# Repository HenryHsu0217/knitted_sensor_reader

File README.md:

# Knitted Sensor Reader

## Introduction
This project contains the code and hardware setup for collecting data from knitted sensors. It includes simple examples of collected data with a 3x10 size sensor and a trained neural network for predicting the angle of the tested sensor. Additionally, code is provided for live evaluation for one or four sensors at a time with the trained neural network model.

## Table of Contents
- [Introduction](#introduction)
- [Features](#features)
- [Installation](#installation)
- [Setup](#setup)
    - [Hard ware setup](#hard-ware-setup)
        - [Robot arm setup and control](#robot-arm-setup-and-control)
        - [Xiao Seeed setup](#xiao-seeed-setup)
    - [WiFi setup](#wifi-setup)
- [Usage](#usage)
  - [Data Collection](#data-collection)
    - [Data Collection for one sensor](#data-collection-for-one-sensor)
    - [Data Collection for four sensor](#data-collection-for-four-sensor)
  - [Model Training](#model-training)
  - [Live Evaluation](#live-evaluation)
- [Examples](#examples)
## Features
- Collect data from knitted sensors
- Simple examples with 3x10 size sensor data
- Trained neural network model for angle prediction
- Live evaluation for one or four sensors simultaneously
## Installation
1. Clone the repository to your local machine:
   ```sh
   git clone https://github.com/HenryHsu0217/knitted_sensor_reader.git
    ```
2. Navigate to the project directory
3. Install the required dependencies:
    ```sh
    pip install -r requirements.txt
    ```
## Setup
### Hard ware setup
To set up the hardware for this project, you will need:  
- Knitted sensors
- Xiao Seeed ESP32C with custom PCB
- Connection wires
- Batteries
- Arduino Tinkerkit robot arm with sleeve and Ardino Uno
#### Robot arm setup and control
To setup and control the robot arm, please first go to https://docs.arduino.cc/retired/getting-started-guides/Braccio/ to check the essential library for the robot, after downloading the library, upload `Robot_arm.cpp` to the braod controling the arm. After uploading, you can control the robot arm to certain angle with serial input. Before entering the angle, please keep in mind that we are only controlling the ELBOW of the robot, and due to the setting of the arm, the arm will be at 0 degree with a setting of 45, so when entering the desired angle remember to add 45 to it. For example if you want the ELBOW to got to 60 degree, please enter 105 instead.
  
Attach the knitted sensor to the robot arm with pib needle to finish the robot arm setup.
### WiFi setup
The device that you are running the code with will be the server for the system, and make sure you are connected to private network, pubic network may cuase problem in connection.  

After your device is connected to a private netwrok and get your device's IP address update the SSID, password, and host ID accroding to your device in the `WiFi_Client.cpp` file for the Xiao Seeed broad. And also remember to update the host IP in `server_for_one.py`, `server_for_four.py`, `Live_Evalution_for_one.py`, and `live_Evalution_for_four.py` before running them with your device's IP.
#### Xiao Seeed setup
Upload `WiFi_Client.cpp` to the broad with the WiFi set correctly, insert the wires from the knitted sensor into the terminal and screw it tight. Plug in the battery and after the server is running press reset button on the broad to connect to the server.
  
After all the setups, you are ready to run the server for data collection, you can check the finished setup image of the robot arm in the `images` directory. Furthermore you can find files for the PCB in the `PCB` directory, you can open it with KiCad.
## Usage
### Data collection 
#### Data collection for one sensor
Before running the file `server_for_one.py` once again make sure the WiFi has been setup properly so that the port and host IP in `server_for_one.py` are the same in `WiFi_Client.cpp`. After uploading `WiFi_Client.cpp` to the braod and `server_for_one.py`.  

Run the server with:
```sh
python server_for_one.py
```  
After running the command line would show:
```sh
Server listening on 172.20.10.3:8080
starting user thread
Please input the file location for the data: 
```  
Enter the file location that you want to save the data(Ex: `datas/test_file`). After entering the file location the command line will ask to enter the current angle:
```sh
Please input angle: 
```
 After entering the angle, connect power to the Xiao Seed broad, if nothing happens press the reset button on the broad to make it retry on connecting to the WiFi. After it is connected to WiFi and connected to the server, the command line would show:
```sh
Server listening on 172.20.10.3:8080
starting user thread
Please input the file location for the data: test_file
Accepted connection from ('172.20.10.5', 51490)
```  
Than you can start collecting by entering `start` in the command line and press enter. Then the data will start logging and show the datas in the command line as:
```sh
Logging: 651 4088
Logging: 652 4090
Logging: 653 4092
Logging: 654 4091
Logging: 655 4092
```  
When finished, to save the file, simpliy enter `log` and press enter to save the file(the command line will keep refreshing the output so don't worry if your input is over write by the out put). Then you can find the data in the location that you defined earlier.  
  
After entering `log`, the process will stop, saving the file and start asking you for file location agian, you can continue with the next data collection directly with the same step: enter the desired location, enter start(no need for rest of the broad), enter `log` if finished. And if done with the entire process, enter `e` to stop the program and shut down the server.
#### Data collection for four sensor
For collecting data for four sensor, the process is simillar with the previous one, be fore running the `sever_for_four.py` file make sure the IP, port and other requirements are enter correclty for `sever_for_four.py` and `WiFi_Client.cpp`.  
  
Prepare 4 Xiao Seeed broad with code uploded to them, connect power to them and start the server with:
```sh
python sever_for_four.py
```  
After running the command line will show the same thing as:
```sh
Server listening on 172.20.10.3:8080
starting user thread
Please input the file location for the data: 
```  
Then same enter the file name and location you want to save the data. Then the command line will ask to enter the angles for the 4 sensors:
```sh
Please input angles separate with space: 
```
Enter the angle(Ex:10 20 30 40), the angles are the real angle of each broads, and how the broads are labeled is accroding to the sequence of the broad is connected to the server. For example is board 1 is connected first then it will be asigned with the angle label of 10 and so on.

Next press the reset button on the broads, and as they reset and connected to the server, the command line will output:
```sh
Waiting for connection: [1/4]
Waiting for connection: [2/4]
Waiting for connection: [3/4]
Waiting for connection: [4/4]
```
When all broad is connected, enter `start` and enter to start the data collection, then the command line will output the readings of the 4 broad:
```sh
Device  1 : 4092 Device  2 : 4089 Device  3 : 4094 Device  4 : 4091
```  
To save the data first enter `log`, this will stop the process and fetch the datas from all 4 broads, then enter `save` to save the file to the location entered earlier. And same after saving, the command line will ask you to enter the location for saving the data again, you can then start your next collection direclty by repeating the same process(there some time will have output bugs, which the output of the command line doesn't match what is mentioned above, but you can ignore it and follow the same input process).
### Model Training for one sensor
After data collection, a model can be trained with the data to predict the angle of the knitted senor. In the `NeuralNetwork` directory there is a pre-defined netwrork `Network_for_one.py` for training a model to predict the angle for only one sensor.  

Before training, since the data for one sensor is stored separated with different angle, we will want to mege them. To merge the data into single one for training, use the `merge.py` file in `datas/` which replace the file name in the code with the file directoryof your data, and it will merge the data into one and store into `datas/Merged`.  
  
After merging the data, you can replace the file name in `Train_for_one.py` to your merged data for training, and you can tune the hyperparameter there. After training, the trained model will be saved in `./NerualNetwork/Trained_models`.
### Evaluating the trained model
To evaluate the trained model, you can use `Evaluate.py` to evaluate the trained model's performence on a specific dataset, for `Live_Evaluation_for_one.py` and `Live_Evaluation_for_four.py` you can see the prediction of the reading with the sensor in action.  
  
The usage of `Evaluate.py` is straight forward, replace the path to your dataset that you want to use for testing the model and the model you want to test. The code will test the model with your dataset and count the number of prediction that has errors under 5, 10, 20, and 30 degree, if the errors are under 5 then we see it as correct otherwise incorrect. At the end the code will output the number of correct predictions and incorrect predictions and the accuraccy of the model.  
  
To run `Live_Evaluation_for_one.py` and `Live_Evaluation_for_four.py`, refer to the [Data Collection](#data-collection) section which it is very simillar. After the broads are connected to the server, enter `start` and the code will then output the prediction of the angle of the sensor, and enter `e` to stop.

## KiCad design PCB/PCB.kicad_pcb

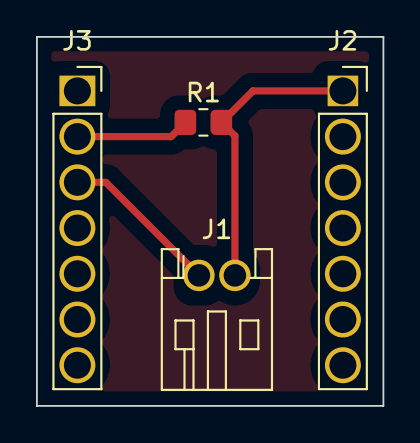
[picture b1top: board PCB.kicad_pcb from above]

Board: 2 copper layers, 19.2 x 20.5 mm, 4 parts (0 on the bottom side), 3 nets.

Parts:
J1: Conn_01x02_Female; JST_PH_S2B-PH-K_1x02_P2.00mm_Horizontal
J2, J3: Conn_01x07_Female; PinSocket_1x07_P2.54mm_Vertical
R1: 155; R_0805_2012Metric_Pad1.20x1.40mm_HandSolder

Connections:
3.3V: J1.1, J3.3
A0: J2.1, R1.2
GND: J3.2, R1.1

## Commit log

2024-05-21 Live evaluation for four sensor
2024-05-21 Update of read.md file and images
2024-05-21 Images
2024-05-21 Added Arduino code, add angle entering functionality and images
2024-05-22 READ file update
2024-05-22 Update read me
2024-05-22 Read file update and PCB file
2024-05-23 Fixed importing proble in NerualNetwork
2024-05-30 .DS_Store
